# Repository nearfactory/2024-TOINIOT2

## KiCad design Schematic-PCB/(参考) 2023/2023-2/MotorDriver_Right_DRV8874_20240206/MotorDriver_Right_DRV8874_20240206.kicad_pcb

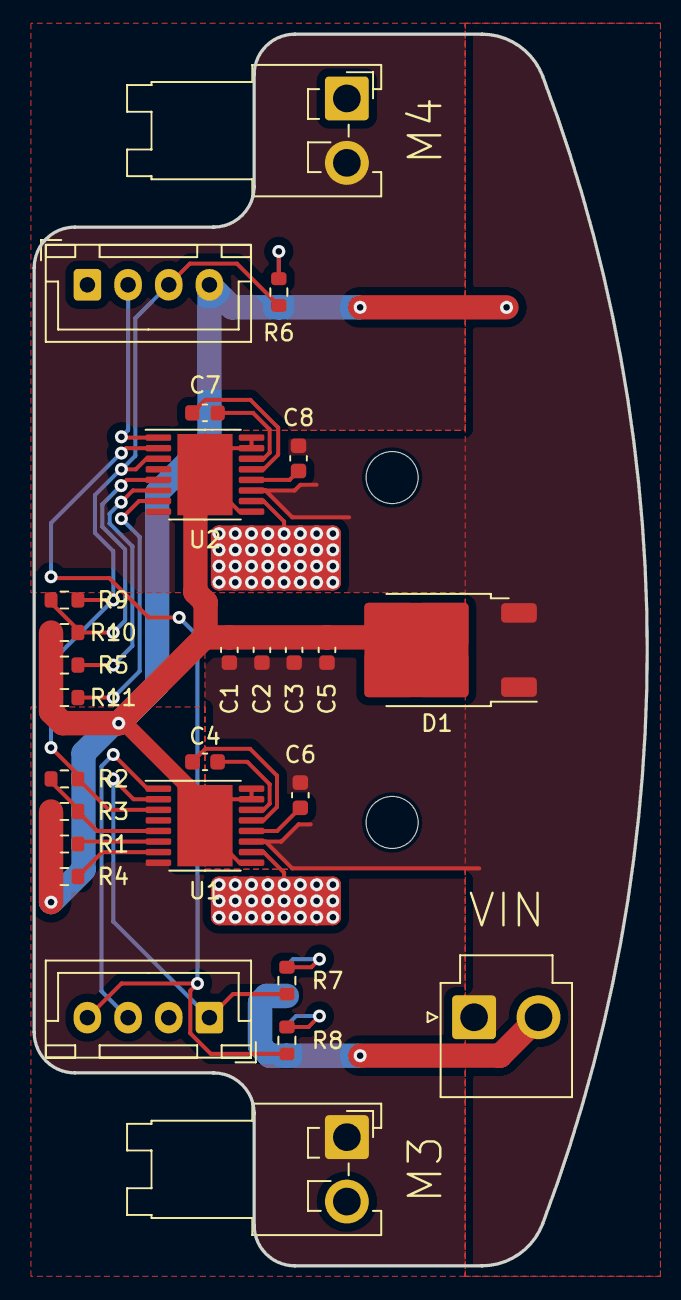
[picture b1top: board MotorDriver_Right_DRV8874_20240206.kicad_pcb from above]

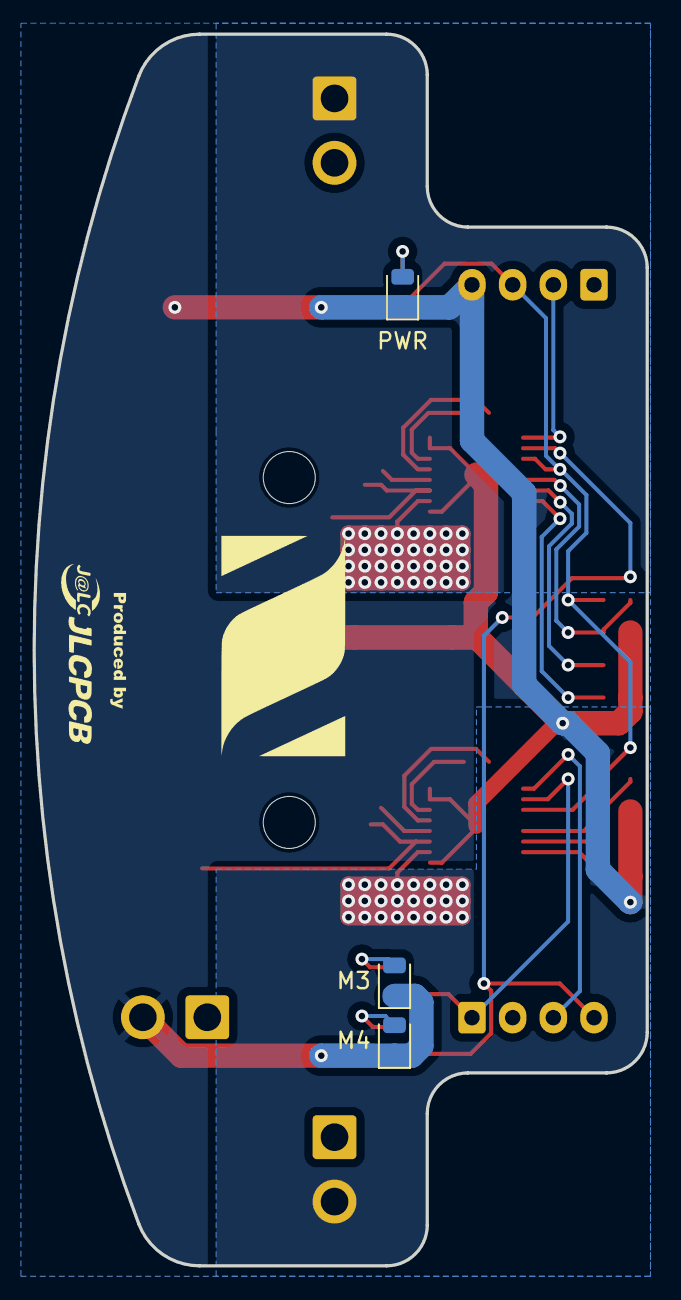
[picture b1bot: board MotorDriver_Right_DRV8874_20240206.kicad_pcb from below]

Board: 2 copper layers, 37.7 x 75.7 mm, 30 parts (3 on the bottom side), 26 nets.

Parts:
C1, C2: 4.7uF; C_0603_1608Metric
C3, C5: 0.1uF; C_0603_1608Metric
C4, C7: 22nF; C_0603_1608Metric
C6, C8: 220nF; C_0603_1608Metric
D1: D_Schottky_AKA; TO-252-2
J4, J5: Conn_01x04_Pin; JST_XH_B4B-XH-A_1x04_P2.50mm_Vertical
M3, M4: Conn_01x02_Pin; JST_VH_S2P-VH_1x02_P3.96mm_Horizontal
M3#2, M4#2: LED; LED_0805_2012Metric
PWR: LED; LED_0805_2012Metric
R1, R5: 2.49K; R_0603_1608Metric
R2, R9: 10K; R_0603_1608Metric
R3, R10: NP; R_0603_1608Metric
R4, R11: 20K; R_0603_1608Metric
R6, R7, R8: 330; R_0603_1608Metric
U1, U2: HTSSOP-16-1EP_4.4x5mm_P0.65mm_EP3.4x5mm_Mask2.46x2.31mm_The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
VIN: Conn_01x02_Pin; JST_VH_B2P-VH-B_1x02_P3.96mm_Vertical

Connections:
EN-1: J4.3, U1.1 (EN)
EN-2: J5.2, U2.1 (EN)
GND: C1.2, C2.2, C3.2, C5.2, D1.2 (K), J5.4, M3#2.1 (K), M4#2.1 (K), PWR.1 (K), R1.1, R3.2, R4.2, R5.1, R10.2, R11.2, U1.9 (PGND), U1.15 (GND), U1.16 (PMODE), U1.17 (PAD), U2.9 (PGND), U2.15 (GND), U2.16 (PMODE), U2.17 (PAD), VIN.2
IMODE-1: R4.1, U1.7 (IMODE)
IMODE-2: R11.1, U2.7 (IMODE)
unnamed: PWR.2 (A), R6.2
unnamed: M3#2.2 (A), R7.2
unnamed: M4#2.2 (A), R8.2
unnamed: C4.2, U1.13 (CPH)
unnamed: C4.1, U1.14 (CPL)
unnamed: R1.2, U1.6 (IPROPI)
unnamed: C6.1, U1.12 (VCP)
unnamed: C7.2, U2.13 (CPH)
unnamed: C7.1, U2.14 (CPL)
unnamed: R5.2, U2.6 (IPROPI)
unnamed: C8.1, U2.12 (VCP)
OUT1-1: M3.1, U1.8 (OUT1)
OUT1-2: M4.2, U2.8 (OUT1)
OUT2-1: M3.2, U1.10 (OUT2)
OUT2-2: M4.1, U2.10 (OUT2)
PH-1: J4.1, R7.1, U1.2 (PH)
PH-2: J4.4, R8.1, U2.2 (PH)
SLEEP-1: J5.3, R2.1, R6.1, R9.1, U1.3 (SLEEP), U2.3 (SLEEP)
VIN: C1.1, C2.1, C3.1, C5.1, C6.2, C8.2, D1.1 (A), D1.3 (A), U1.11 (VM), U2.11 (VM), VIN.1
VREF-1: R2.2, R3.1, U1.5 (VREF)
VREF-2: R9.2, R10.1, U2.5 (VREF)

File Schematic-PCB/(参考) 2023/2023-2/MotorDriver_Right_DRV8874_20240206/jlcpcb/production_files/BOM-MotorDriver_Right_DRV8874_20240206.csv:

Comment,Designator,Footprint,LCSC
0.1uF,"C3,C5",C_0603_1608Metric,C14663
~,"U1,U2",HTSSOP-16-1EP_4.4x5mm_P0.65mm_EP3.4x5mm_Mask2.46x2.31mm_ThermalVias,C1855818
4.7uF,"C1,C2",C_0603_1608Metric,C19666
220nF,"C6,C8",C_0603_1608Metric,C21120
22nF,"C4,C7",C_0603_1608Metric,C21122
2.49K,"R1,R5",R_0603_1608Metric,C22908
330,"R6,R7,R8",R_0603_1608Metric,C23138
10K,"R2,R9",R_0603_1608Metric,C25804
20K,"R11,R4",R_0603_1608Metric,C4184
D_Schottky_AKA,D1,TO-252-2,C668192

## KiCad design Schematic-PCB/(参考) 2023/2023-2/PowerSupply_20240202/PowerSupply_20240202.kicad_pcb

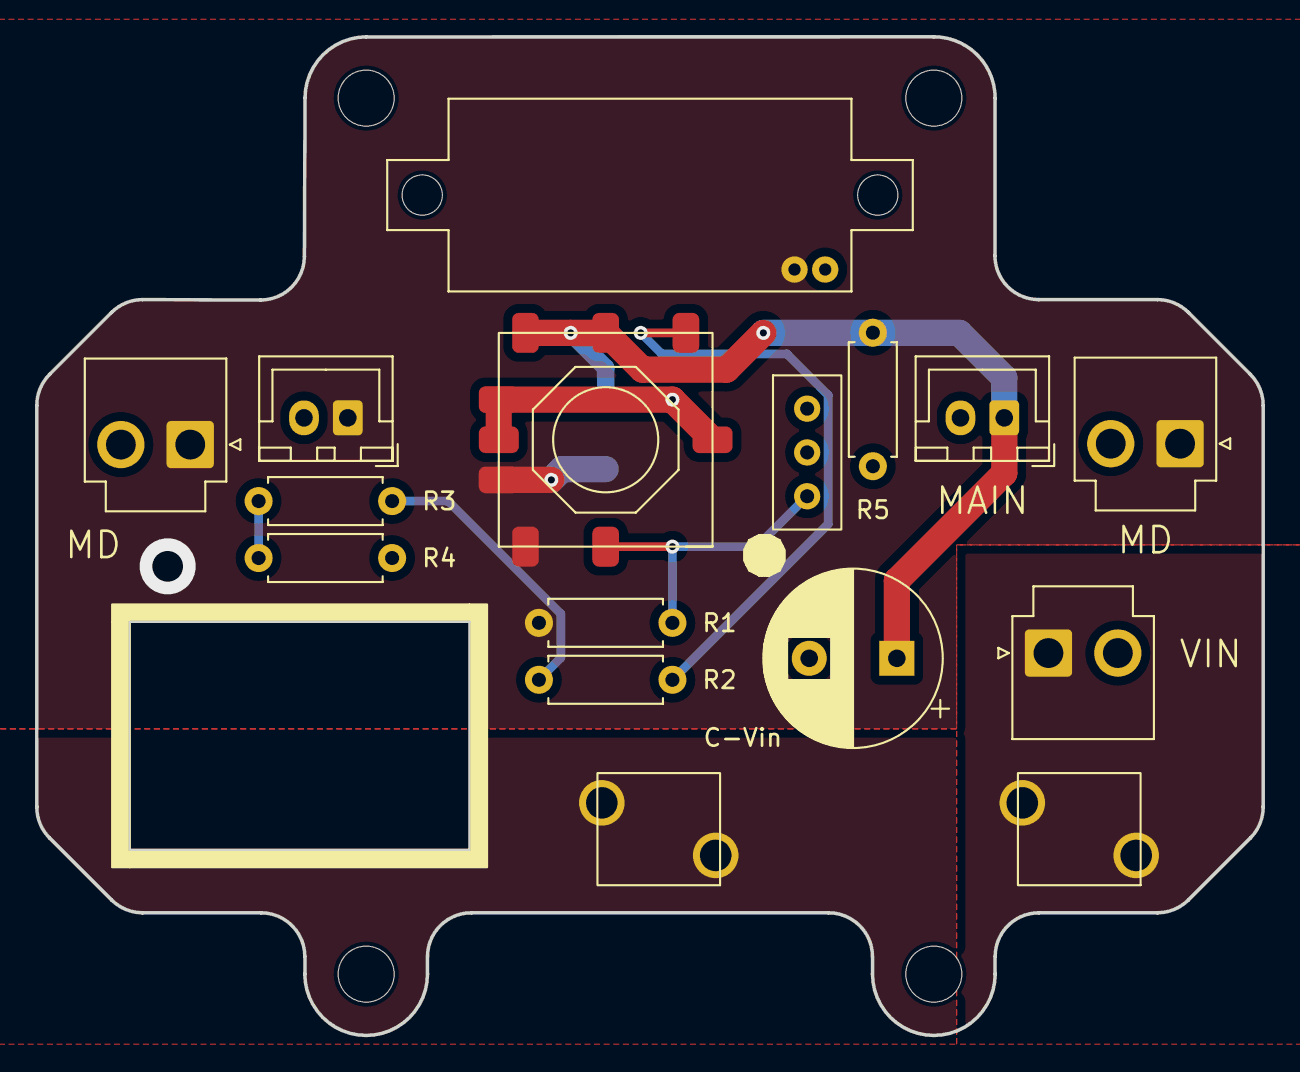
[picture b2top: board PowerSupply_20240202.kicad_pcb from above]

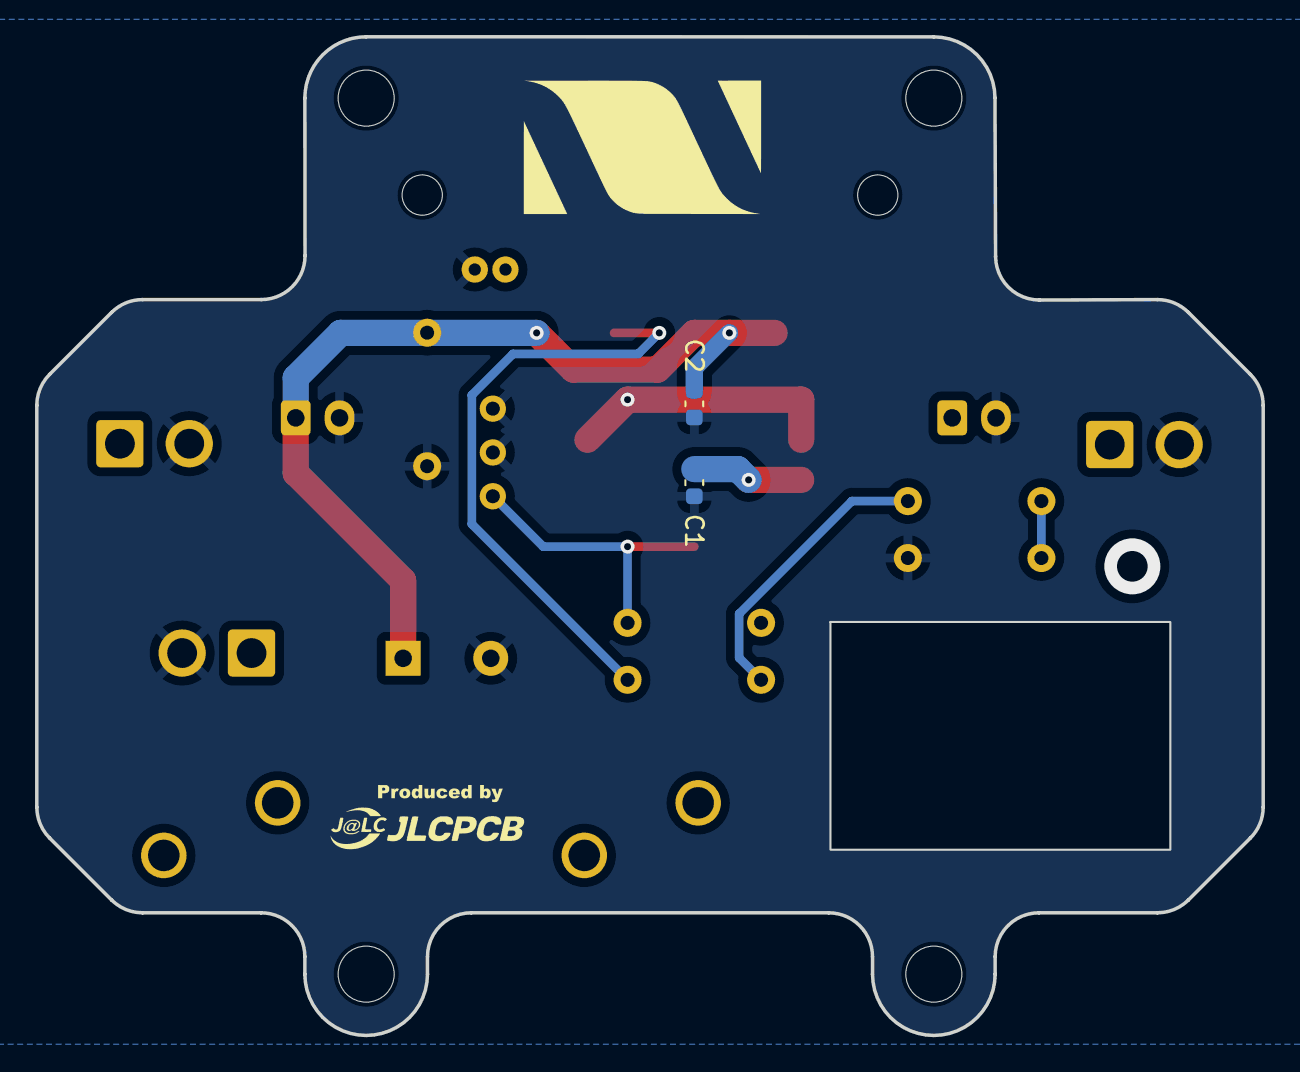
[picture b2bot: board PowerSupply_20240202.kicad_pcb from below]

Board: 2 copper layers, 70.0 x 57.0 mm, 18 parts (2 on the bottom side), 8 nets.

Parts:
C1: 22uF; C_0603_1608Metric
C2: 10uF; C_0603_1608Metric
C-Vin: 1000uF; CP_Radial_D10.0mm_P5.00mm
F1: Fuse
MAIN: Main; JST_XH_B2B-XH-A_1x02_P2.50mm_Vertical
MD: MD; JST_VH_B2P-VH-B_1x02_P3.96mm_Vertical
MD#2: MD; JST_VH_B2P-VH-B_1x02_P3.96mm_Vertical
MES1: Voltmeter_DC; VoltMeter
R1: 20K; R_Axial_DIN0207_L6.3mm_D2.5mm_P7.62mm_Horizontal
R2: 1K; R_Axial_DIN0207_L6.3mm_D2.5mm_P7.62mm_Horizontal
R3: 330; R_Axial_DIN0207_L6.3mm_D2.5mm_P7.62mm_Horizontal
R4: 10; R_Axial_DIN0207_L6.3mm_D2.5mm_P7.62mm_Horizontal
R5: 1.2K; R_Axial_DIN0207_L6.3mm_D2.5mm_P7.62mm_Horizontal
SW1: SW_SPST; RA1113112R
SW2: SW_SPDT; SS12D01G4
U1: OKL-T6-W12N-C
VIN: Battery; JST_VH_B2P-VH-B_1x02_P3.96mm_Vertical
Voltage: Kicker; JST_XH_B2B-XH-A_1x02_P2.50mm_Vertical

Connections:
+5V: C2.1, C-Vin.1, MAIN.1, R5.1, U1.4 (Vout), U1.5 (Sense)
GND: C1.2, C2.2, C-Vin.2, MAIN.2, MD.2, MD#2.2, MES1.1 (-), R4.2, R5.2, SW2.2 (B), SW2.3 (C), U1.3 (GND), U1.7 (GND), VIN.2, Voltage.2
unnamed: F1.1, VIN.1
unnamed: R2.2, R3.2
unnamed: R3.1, R4.1
unnamed: R1.1, SW2.1 (A), U1.1 (ON/OFF)
unnamed: R2.1, U1.6 (Trim)
VIN: C1.1, MD.1, MD#2.1, MES1.2 (+), R1.2, U1.2 (Vin), Voltage.1

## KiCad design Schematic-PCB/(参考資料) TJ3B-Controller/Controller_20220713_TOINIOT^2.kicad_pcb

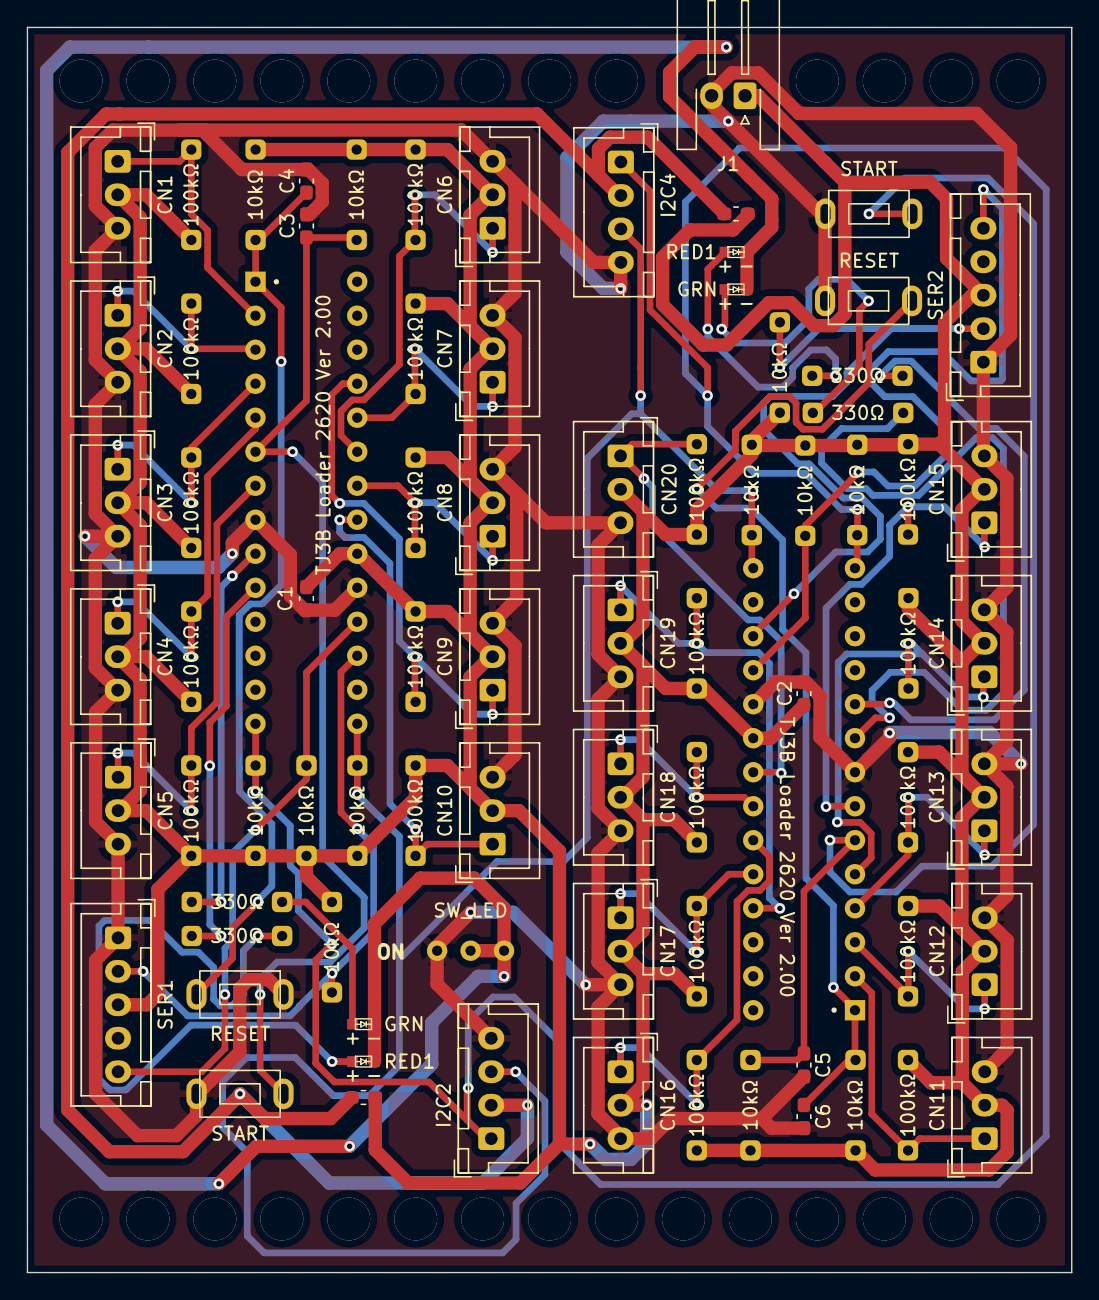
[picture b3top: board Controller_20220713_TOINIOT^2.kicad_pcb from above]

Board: 2 copper layers, 78.0 x 93.0 mm, 80 parts (0 on the bottom side), 42 nets.

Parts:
C1, C2, C3, C4, C5, C6: C; C_0603_1608Metric_Pad1.08x0.95mm_HandSolder
CN1, CN2, CN3, CN4, CN5, CN6, CN7, CN8, CN9, CN10, CN11, CN12, CN13, CN14, CN15, CN16, CN17, CN18, CN19, CN20: Conn_01x03_Male; JST_XH_B3B-XH-A_1x03_P2.50mm_Vertical
FB2, FB4: FerriteBead; L_0603_1608Metric_Pad1.05x0.95mm_HandSolder
GRN1, GRN2: LED; SMLE13WBC8W1 LED_SMD_1608
I2C2, I2C4: Conn_01x04_Male; JST_XH_B4B-XH-A_1x04_P2.50mm_Vertical
J1: Conn_01x02_Male; JST_XH_S2B-XH-A-1_1x02_P2.50mm_Horizontal
R1, R2, R3, R4, R5, R6, R7, R8, R9, R10, R51, R52, R53, R54, R55, R56, R57, R58, R59, R60: 100kR; R 抵抗
R11, R12, R13, R14, R39, R41, R61, R62, R63, R64, R89, R91: 10kR; R 抵抗
R15, R16: 330Ω; R 抵抗
R65: 470Ω; R 抵抗
R66: 150Ω; R 抵抗
RED1, RED2: LED; SMLE13WBC8W1 LED_SMD_1608
SER1, SER2: Conn_01x05_Male; JST_XH_B5B-XH-A_1x05_P2.50mm_Vertical
SW1, SW3: DTS25N; TVBP06-B043C-B タクトスイッチ小
SW2, SW4: DTS62K; TVBP06-B043C-B タクトスイッチ小
SW_LED: SW_DPDT_x2; SS12D01G4 スライドスイッチ
U1, U2: PIC18F2620; PIC16F2620 TJ3BCore CPU

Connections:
+5V: C1.1, C2.1, CN1.2, CN2.2, CN3.2, CN4.2, CN5.2, CN6.2, CN7.2, CN8.2, CN9.2, CN10.2, CN11.2, CN12.2, CN13.2, CN14.2, CN15.2, CN16.2, CN17.2, CN18.2, CN19.2, CN20.2, FB2.1, FB4.1, J1.1, R1.1, R2.1, R3.1, R4.1, R5.1, R6.1, R7.1, R8.1, R9.1, R10.1, R11.1, R12.1, R13.1, R14.1, R39.1, R41.1, R51.1, R52.1, R53.1, R54.1, R55.1, R56.1, R57.1, R58.1, R59.1, R60.1, R61.1, R62.1, R63.1, R64.1, R89.1, R91.1, SER1.3, SER2.3, U1.20 (VDD), U2.20 (VDD)
+5V_I2C: FB2.2, FB4.2, I2C2.2, I2C4.2
AD1: CN1.1, R1.2, U1.2 (AD1)
AD1_2: CN11.1, R55.2, U2.2 (AD1)
AD2: CN2.1, R2.2, U1.3 (AD2)
AD2_2: CN12.1, R54.2, U2.3 (AD2)
AD3: CN3.1, R3.2, U1.4 (AD3)
AD3_2: CN13.1, R53.2, U2.4 (AD3)
AD4: CN4.1, R4.2, U1.5 (AD4)
AD4_2: CN14.1, R52.2, U2.5 (AD4)
AD5: CN5.1, R5.2, U1.7 (AD5)
AD5_2: CN15.1, R51.2, U2.7 (AD5)
AD6: CN6.1, R6.2, U1.23 (AD6)
AD6_2: CN16.1, R56.2, U2.23 (AD6)
AD7: CN7.1, R7.2, U1.24 (AD7)
AD7_2: CN17.1, R57.2, U2.24 (AD7)
AD8: CN8.1, R8.2, U1.22 (AD8)
AD8_2: CN18.1, R58.2, U2.22 (AD8)
AD9: CN9.1, R9.2, U1.25 (AD9)
AD9_2: CN19.1, R59.2, U2.25 (AD9)
AD10: CN10.1, R10.2, U1.21 (AD10)
AD10_2: CN20.1, R60.2, U2.21 (AD10)
GND: C1.2, C2.2, C3.2, C4.2, C5.2, C6.2, CN1.3, CN2.3, CN3.3, CN4.3, CN5.3, CN6.3, CN7.3, CN8.3, CN9.3, CN10.3, CN11.3, CN12.3, CN13.3, CN14.3, CN15.3, CN16.3, CN17.3, CN18.3, CN19.3, CN20.3, I2C2.4, I2C4.4, J1.2, SER1.1, SER2.1, SW1.2, SW2.2, SW3.2, SW4.2, SW_LED.1 (A), U1.8 (GND), U1.19 (VSS), U2.8 (GND), U2.19 (VSS)
LED_GND: GRN1.1 (K), GRN2.1 (K), RED1.1 (K), RED2.1 (K), SW_LED.2 (B), SW_LED.3 (C)
MCLR: C4.1, R13.2, SW2.1, U1.1 (MCLR)
MCLR_2: C6.1, R63.2, SW4.1, U2.1 (MCLR)
MON_LED: R16.2, U1.10 (MON_LED)
MON_LED_2: R66.2, U2.10 (MON_LED)
unnamed: GRN1.2 (A), R15.1
unnamed: GRN2.2 (A), R65.1
unnamed: R16.1, RED1.2 (A)
unnamed: R66.1, RED2.2 (A)
PWR_LED: R15.2, U1.9 (PWR_LED)
PWR_LED_2: R65.2, U2.9 (PWR_LED)
RA4: C3.1, R14.2, SW1.1, U1.6 (RA4)
RA4_2: C5.1, R64.2, SW3.1, U2.6 (RA4)
RX: R41.2, SER1.5, U1.18 (RX)
RX_2: R91.2, SER2.5, U2.18 (RX)
SCL: I2C2.1, I2C4.1, R11.2, R61.2, U1.14 (SCL), U2.14 (SCL)
SDA: I2C2.3, I2C4.3, R12.2, R62.2, U1.15 (SDA), U2.15 (SDA)
TX: R39.2, SER1.2, U1.17 (TX)
TX_2: R89.2, SER2.2, U2.17 (TX)

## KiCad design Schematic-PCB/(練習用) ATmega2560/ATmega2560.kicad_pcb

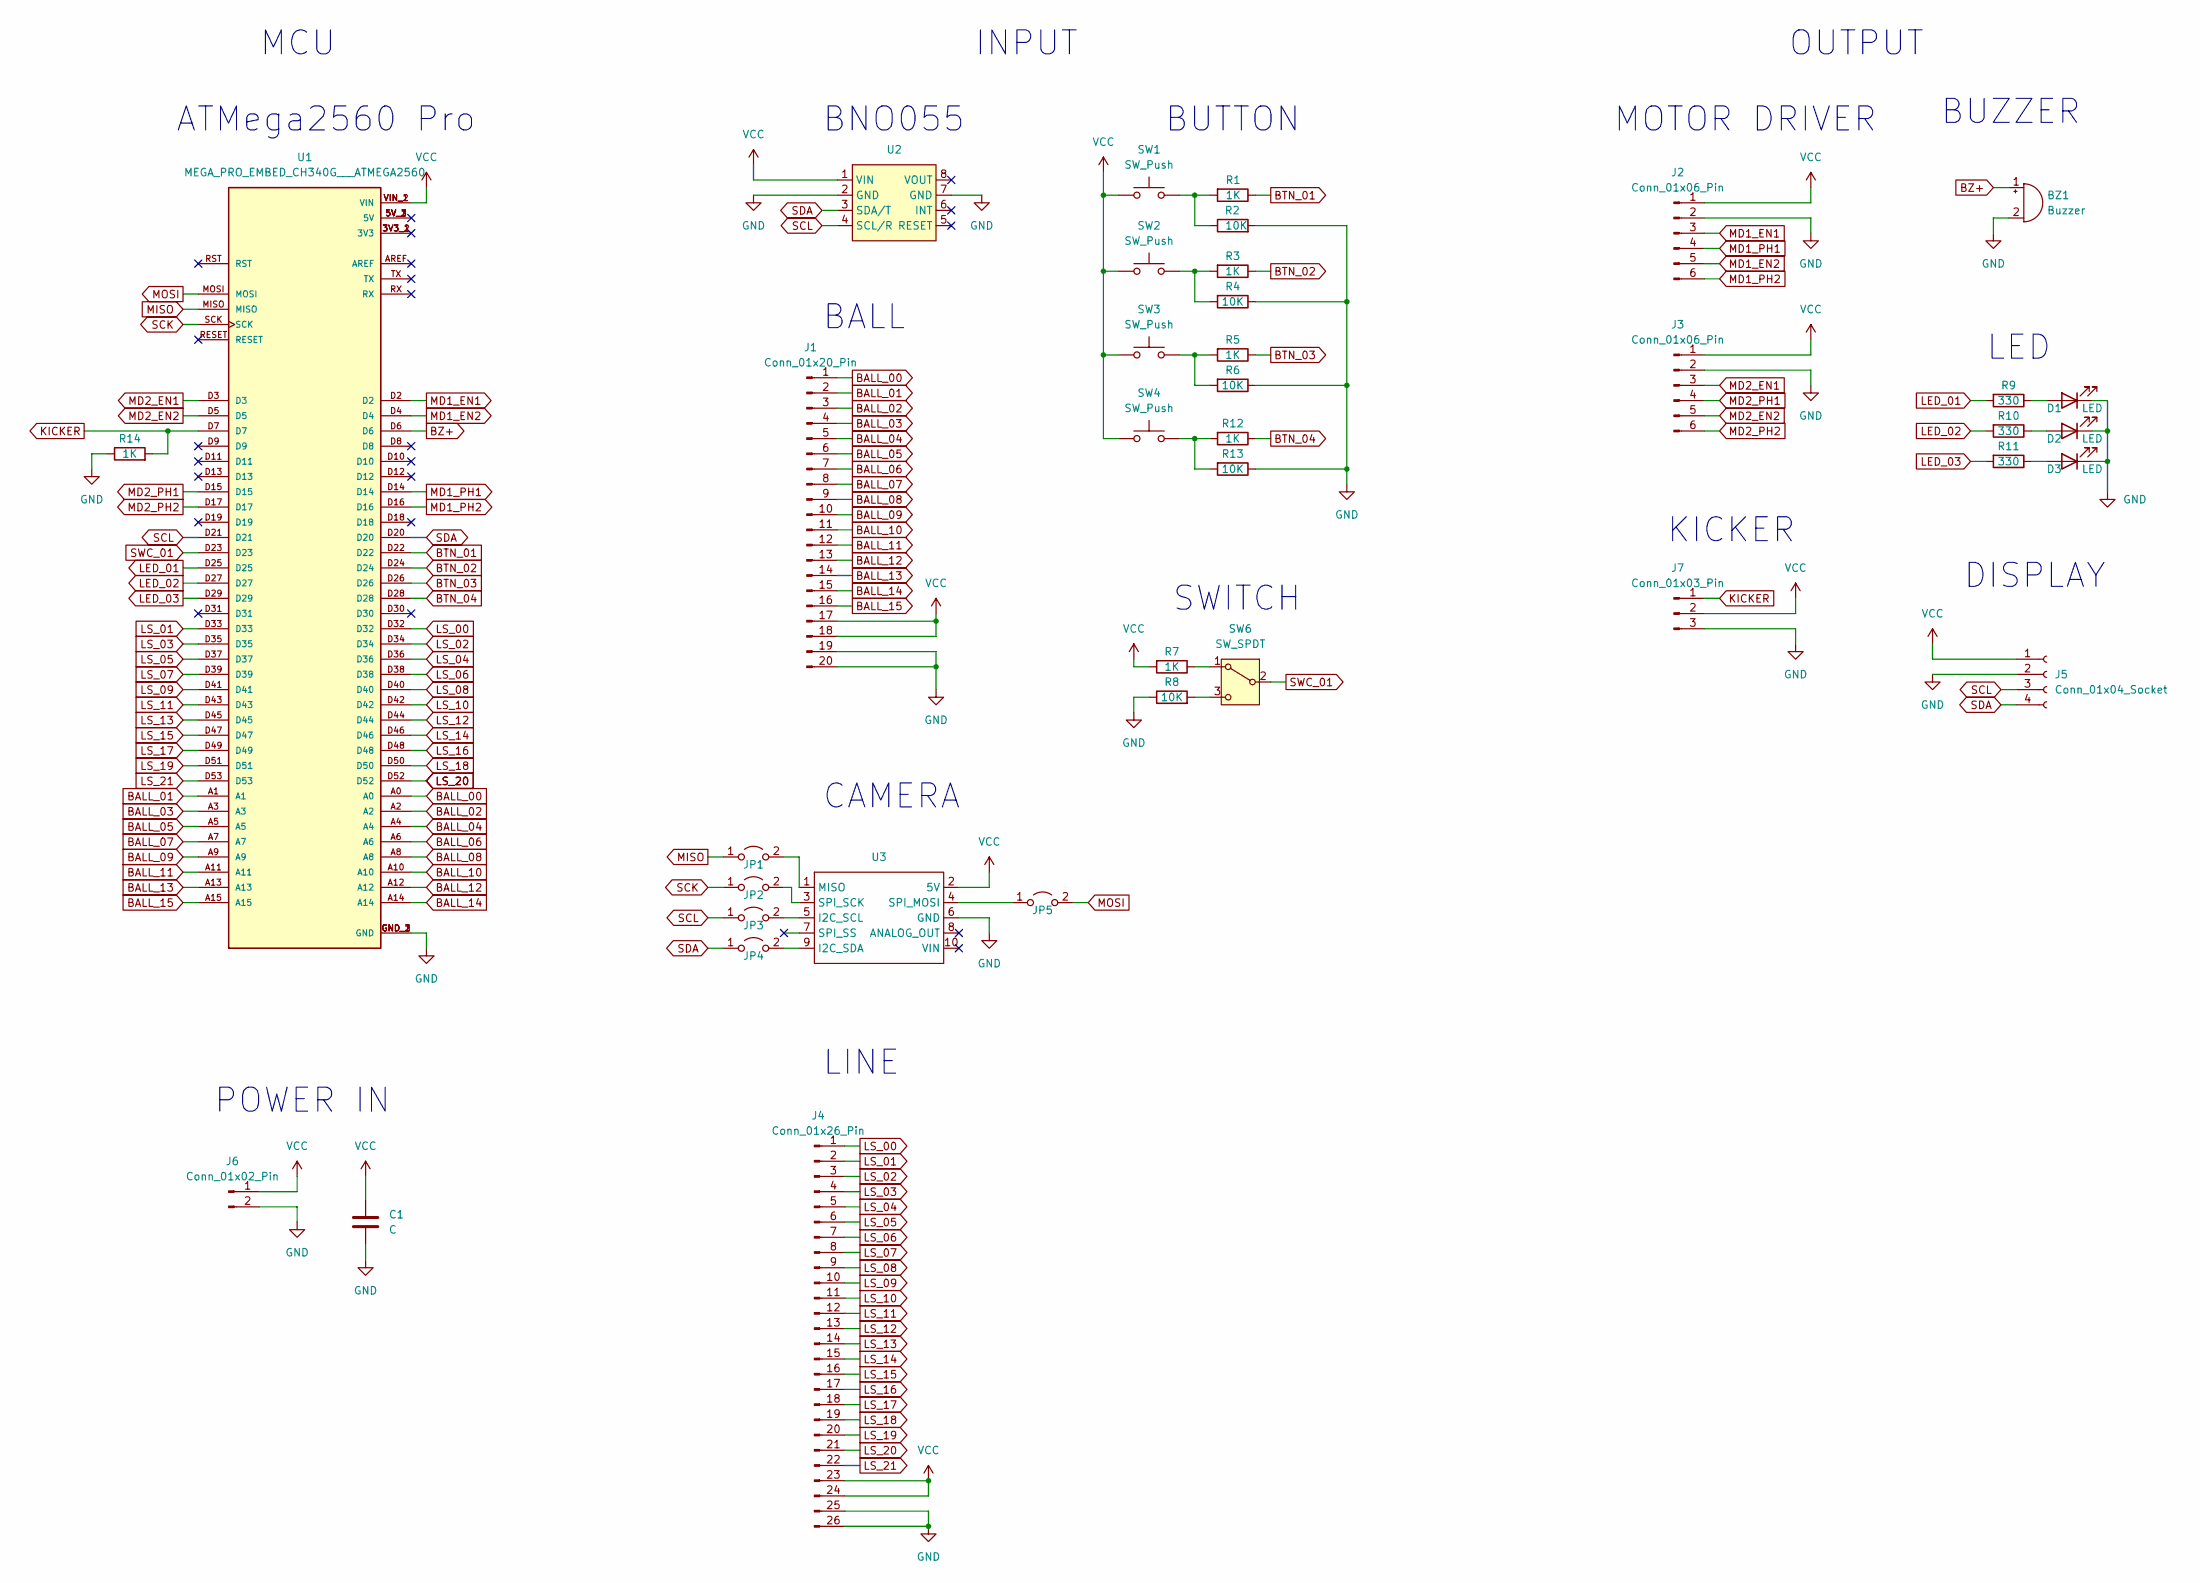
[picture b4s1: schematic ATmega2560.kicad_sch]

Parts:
BZ1: Buzzer; PKM13EPYH4000-A0
C1: C; C_0805_2012Metric
D1, D2, D3: LED; LED_0603_1608Metric
J1: Conn_01x20_Pin; IDC-Header_2x10_P2.54mm_Vertical
J2, J3: Conn_01x06_Pin; JST_XH_B6B-XH-A_1x06_P2.50mm_Vertical
J4: Conn_01x26_Pin; IDC-Header_2x13_P2.54mm_Vertical
J5: Conn_01x04_Socket; PinSocket_1x04_P2.54mm_Vertical
J6: Conn_01x02_Pin; JST_XH_S2B-XH-A-1_1x02_P2.50mm_Horizontal
J7: Conn_01x03_Pin; JST_XH_S3B-XH-A-1_1x03_P2.50mm_Horizontal
JP1, JP2, JP3, JP4, JP5: Jumper_2_Open; SolderJumper-2_P1.3mm_Open_Pad1.0x1.5mm
R1, R3, R5, R7, R12, R14: 1K; R_0805_2012Metric
R2, R4, R6, R8, R13: 10K; R_0805_2012Metric
R9, R10, R11: 330; R_0805_2012Metric
SW1, SW2, SW3, SW4: SW_Push; TVBP06-BN043CB-B
SW6: SW_SPDT; SS12D01G4-G_2
U1: MEGA_PRO_EMBED_CH340G___ATMEGA2560; ATMega2560; PARTREV 12/May/2017
U2: BNO055
U3: IDC-Header_2x05_P2.54mm_Vertical

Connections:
BALL_00: J1.1, U1.A0
BALL_01: J1.2, U1.A1
BALL_02: J1.3, U1.A2
BALL_03: J1.4, U1.A3
BALL_04: J1.5, U1.A4
BALL_05: J1.6, U1.A5
BALL_06: J1.7, U1.A6
BALL_07: J1.8, U1.A7
BALL_08: J1.9, U1.A8
BALL_09: J1.10, U1.A9
BALL_10: J1.11, U1.A10
BALL_11: J1.12, U1.A11
BALL_12: J1.13, U1.A12
BALL_13: J1.14, U1.A13
BALL_14: J1.15, U1.A14
BALL_15: J1.16, U1.A15
BTN_01: R1.1, U1.D22
BTN_02: R3.1, U1.D24
BTN_03: R5.1, U1.D26
BTN_04: R12.1, U1.D28
BZ+: BZ1.1 (+), U1.D6
GND: BZ1.2 (-), C1.2, D1.1 (K), D2.1 (K), D3.1 (K), J1.19, J1.20, J2.2, J3.2, J4.25, J4.26, J5.2, J6.2, J7.3, R2.2, R4.1, R6.1, R8.1, R13.1, R14.1, U1.GND_1 (GND), U1.GND_2 (GND), U1.GND_3 (GND), U2.2 (GND), U2.7 (GND), U3.6 (GND)
KICKER: J7.1, R14.2, U1.D7
LED_01: R9.2, U1.D25
LED_02: R10.2, U1.D27
LED_03: R11.2, U1.D29
LS_00: J4.1, U1.D32
LS_01: J4.2, U1.D33
LS_02: J4.3, U1.D34
LS_03: J4.4, U1.D35
LS_04: J4.5, U1.D36
LS_05: J4.6, U1.D37
LS_06: J4.7, U1.D38
LS_07: J4.8, U1.D39
LS_08: J4.9, U1.D40
LS_09: J4.10, U1.D41
LS_10: J4.11, U1.D42
LS_11: J4.12, U1.D43
LS_12: J4.13, U1.D44
LS_13: J4.14, U1.D45
LS_14: J4.15, U1.D46
LS_15: J4.16, U1.D47
LS_16: J4.17, U1.D48
LS_17: J4.18, U1.D49
LS_18: J4.19, U1.D50
LS_19: J4.20, U1.D51
LS_20: J4.21, U1.D52
LS_21: J4.22, U1.D53
MD1_EN1: J2.3, U1.D2
MD1_EN2: J2.5, U1.D4
MD1_PH1: J2.4, U1.D14
MD1_PH2: J2.6, U1.D16
MD2_EN1: J3.3, U1.D3
MD2_EN2: J3.5, U1.D5
MD2_PH1: J3.4, U1.D15
MD2_PH2: J3.6, U1.D17
MISO: JP1.1 (A), U1.MISO
MOSI: JP5.2 (B), U1.MOSI
unnamed: D1.2 (A), R9.1
unnamed: D2.2 (A), R10.1
unnamed: D3.2 (A), R11.1
unnamed: JP1.2 (B), U3.1 (MISO)
unnamed: JP2.2 (B), U3.3 (SPI_SCK)
unnamed: JP3.2 (B), U3.5 (I2C_SCL)
unnamed: JP4.2 (B), U3.9 (I2C_SDA)
unnamed: JP5.1 (A), U3.4 (SPI_MOSI)
unnamed: R1.2, R2.1, SW1.2
unnamed: R3.2, R4.2, SW2.2
unnamed: R5.2, R6.2, SW3.2
unnamed: R12.2, R13.2, SW4.2
unnamed: R7.1, SW6.1 (A)
unnamed: R8.2, SW6.3 (C)
SCK: JP2.1 (A), U1.SCK
SCL: J5.3, JP3.1 (A), U1.D21, U2.4 (SCL/R)
SDA: J5.4, JP4.1 (A), U1.D20, U2.3 (SDA/T)
SWC_01: SW6.2 (B), U1.D23
VCC: C1.1, J1.17, J1.18, J2.1, J3.1, J4.23, J4.24, J5.1, J6.1, J7.2, R7.2, SW1.1, SW2.1, SW3.1, SW4.1, U1.VIN_1 (VIN), U1.VIN_2 (VIN), U2.1 (VIN), U3.2 (5V)

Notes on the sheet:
OUTPUT
DISPLAY
CAMERA
KICKER
ATMega2560 Pro
BNO055
BUTTON
BUZZER
SWITCH
MOTOR DRIVER
BALL
POWER IN
MCU
INPUT
LINE
LED

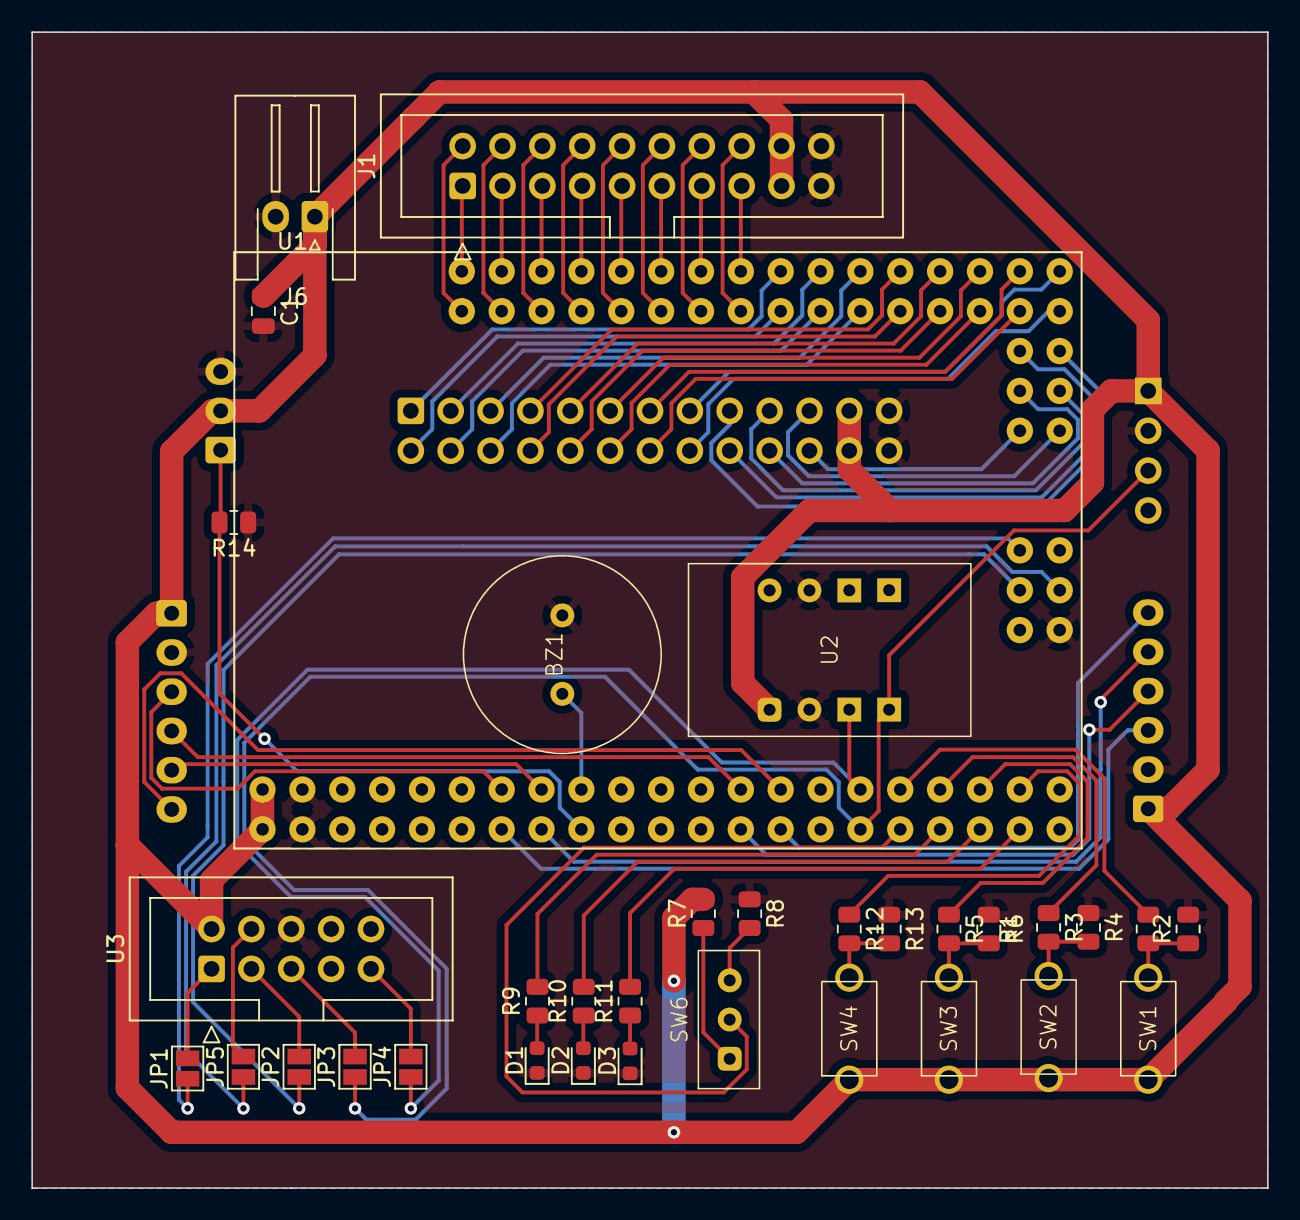
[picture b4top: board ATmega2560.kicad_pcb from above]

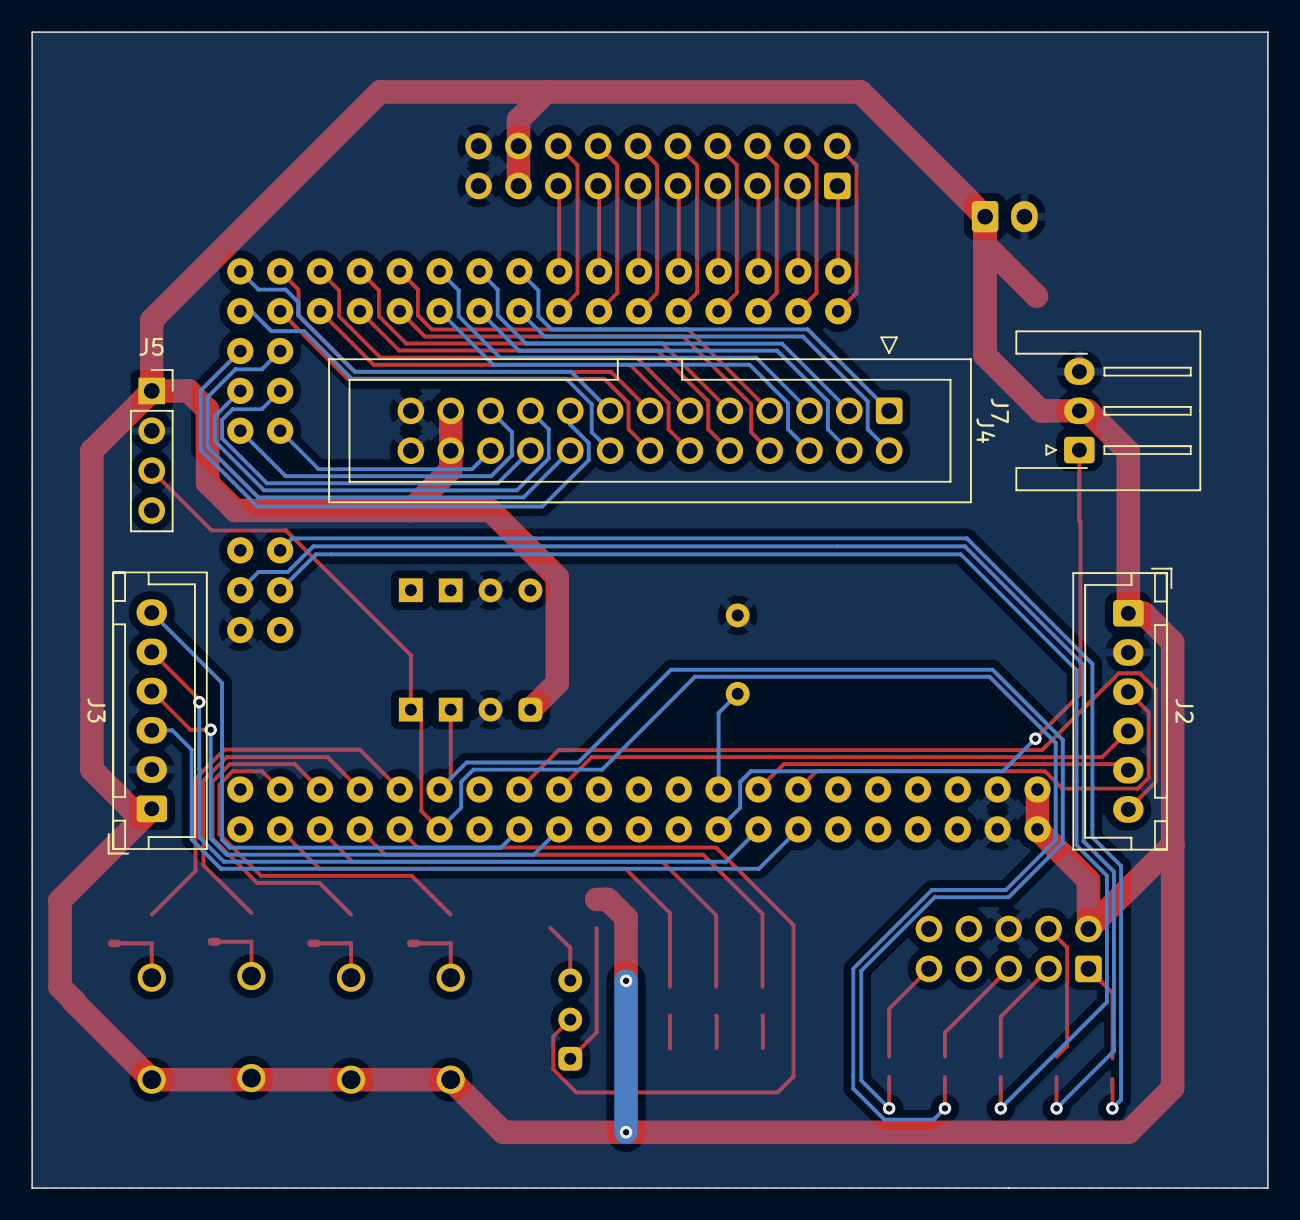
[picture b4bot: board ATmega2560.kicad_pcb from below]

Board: 2 copper layers, 78.7 x 73.7 mm, 39 parts (5 on the bottom side), 77 nets.

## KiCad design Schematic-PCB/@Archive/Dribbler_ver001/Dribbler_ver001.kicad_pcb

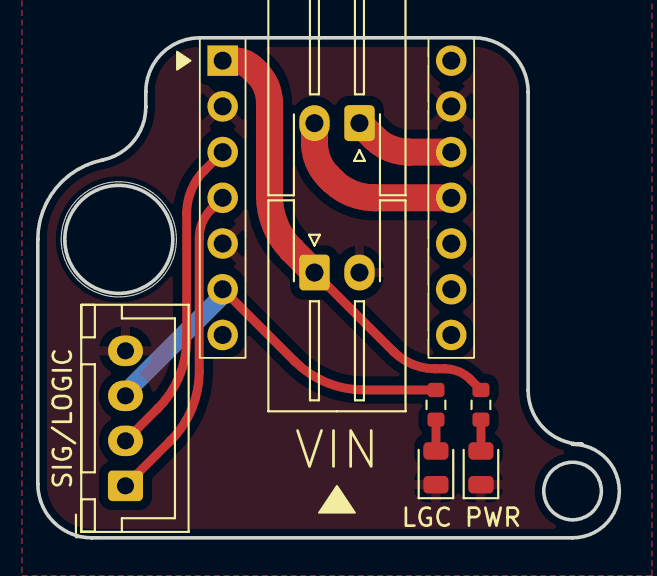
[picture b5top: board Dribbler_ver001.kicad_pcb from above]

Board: 2 copper layers, 32.3 x 27.8 mm, 8 parts (0 on the bottom side), 9 nets.

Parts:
J3: Conn_01x02_Pin; JST_XH_S2B-XH-A-1_1x02_P2.50mm_Horizontal
LGC: Signal; LED_0805_2012Metric
PWR: Power; LED_0805_2012Metric
R1, R2: 330; R_0603_1608Metric
SIG/LOGIC: Conn_01x04_Pin; JST_XH_B4B-XH-A_1x04_P2.50mm_Vertical
U1: DRV8874 module
VIN: Conn_01x02_Pin; JST_XH_S2B-XH-A-1_1x02_P2.50mm_Horizontal

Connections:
+3.3V: R1.2, SIG/LOGIC.3, U1.6 (SLEEP)
EN: SIG/LOGIC.2, U1.3 (EN)
GND: LGC.1 (K), PWR.1 (K), SIG/LOGIC.4, U1.2 (GND), U1.5 (PMODE), U1.13 (GND), VIN.2
unnamed: LGC.2 (A), R1.1
unnamed: PWR.2 (A), R2.1
OUT1: J3.1, U1.12 (OUT1)
OUT2: J3.2, U1.11 (OUT2)
PH: SIG/LOGIC.1, U1.4 (PH)
VCC: R2.2, U1.1 (VM), VIN.1
